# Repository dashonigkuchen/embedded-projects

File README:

# Car seat control (ESP32-C3 / PlatformIO)

Firmware for a DIY car-seat control unit with heating/cooling and battery charging integration.

## Status

- Hardware/feature intent is documented below.
- Current firmware in [src/main.cpp](src/main.cpp) is still the PlatformIO template (no seat-control logic yet).

## What this is (intended)

The overall project is a car seat with:

- Electrical adjustment motors (not handled by this firmware)
- Seat heating and cooling
- A custom battery pack
- A charging module that the ESP32 talks to

This firmware is intended to run on an ESP32-C3 (configured for the Adafruit QT Py ESP32-C3 in [platformio.ini](platformio.ini)).

## Planned functionality

### Heating & cooling control

- A potentiometer provides the user setpoint/input.
- The ESP32 drives heating and cooling via PWM outputs.
- A dedicated “kill/enable” output can disable both heating and cooling.
- Heating also reads a thermistor input; the firmware must enforce temperature safety limits to avoid damage.

### Charging module integration

- Communication with the charging module via I2C.
- An interrupt line from the module to the ESP32 signals events (e.g., charger plugged in).
- An ESP32 output can disable/stop charging (if needed).

### Optional WiFi

- The ESP32 may try to connect to a configured WiFi for monitoring/control.
- WiFi should be power-aware; if it drains too much battery it may be disabled.

## Hardware

This repo contains both firmware and a custom-hardware design.

- Firmware is currently configured for an Adafruit QT Py ESP32-C3 (`adafruit_qtpy_esp32c3` in [platformio.ini](platformio.ini)).
- The KiCad design in [assets/schematics/chris/](assets/schematics/chris/) uses an ESP32-C3 module directly (ESP32-C3-WROOM-02-H4).

### Schematics (screenshots)

These images are exported from the KiCad project and are useful for quickly understanding the blocks:

### Key parts (from the order list)

The order list is in [assets/order/export_cart_20260301_180926.csv](assets/order/export_cart_20260301_180926.csv).

Notable parts from that cart export:

- ESP32 module: ESP32-C3-WROOM-02-H4 (LCSC C2944070), qty 2
- Charger IC: BQ25792RQMR (LCSC C2862876), qty 2 (1–4 cell, up to 5A charger IC)
- Automotive relays: STKF-12V3 (LCSC C771768), qty 10 (12V coil, 15A@14VDC contacts)
- Power MOSFETs: AOD4184A (LCSC C99124), qty 5 (TO-252 / DPAK)
- Small MOSFETs: AO3400A (LCSC C347475), qty 20 (SOT-23)
- Schottky diodes: SS54F (LCSC C5359893), qty 20 (40V / 5A)
- Inductors: CR6045-2R2N (LCSC C7588804), qty 10 (2.2µH)
- NTC thermistor: HNTC-103F3435FA (LCSC C52204610), qty 10 (10k NTC)
- Terminal blocks: MX142R-5.08-08P (LCSC C48688013), qty 1; MX142R-5.08-02P (LCSC C48688007), qty 5

### Signals / nets (as named in the schematic)

If you want the firmware pinout to match the PCB, these are the key named nets to map to ESP32-C3 GPIOs:

- Heater: `HEATER_PWM`, `HEATER_OUT`, `HEATER_POTI`, `HEATER_THERMISTOR`
- Fan/cooling: `FAN_PWM`, `FAN_OUT`, `FAN_POTI`
- Charger (BQ25792): `BQ_SDA`, `BQ_SCL`, `BQ_INT`, `BQ_STAT`, `BQ_CE`, `BQ_ILIM_HIZ`, `BQ_TS`
- Power control: `POWER_EN`, `V_SYSTEM`, `V_SYSTEM_TOGGLE`
- ESP control: `ESP_EN`, `ESP_BOOT`

## Pinout / wiring (from KiCad schematic)

The KiCad schematic places net labels directly on the ESP32-C3 module pins (U1). Based on those labels, the mapping is:

- Heater
	- `HEATER_PWM` -> ESP32-C3 `IO7`
	- `HEATER_POTI` -> ESP32-C3 `TXD`
	- `HEATER_THERMISTOR` -> ESP32-C3 `IO3`

- Fan / cooling
	- `FAN_PWM` -> ESP32-C3 `IO6`
	- `FAN_POTI` -> ESP32-C3 `IO18`

- Charger (BQ25792)
	- `BQ_SDA` -> ESP32-C3 `IO9`
	- `BQ_SCL` -> ESP32-C3 `IO8`
	- `BQ_INT` -> ESP32-C3 `IO19`
	- `BQ_CE` -> ESP32-C3 `IO0`

- USB (debug / flashing)
	- `USB_D+` -> ESP32-C3 `IO2`
	- `USB_D-` -> ESP32-C3 `IO1`

- Boot control
	- `ESP_BOOT` -> ESP32-C3 `IO4`

Notes:

- The schematic also labels `ESP_EN` and `POWER_EN` at pins that are currently named `GND` in the ESP32-C3 symbol. Please verify the custom symbol pinout and/or those net labels before relying on that part of the mapping.

## Build, flash, monitor

Prerequisites:

- PlatformIO (VS Code extension or `pio` CLI)

Commands (from repo root):

- Build: `pio run`
- Upload: `pio run -t upload`
- Serial monitor: `pio device monitor`

If you have multiple serial devices connected, specify the port:

- `pio run -t upload --upload-port /dev/ttyUSB0`
- `pio device monitor --port /dev/ttyUSB0`

## Configuration

TBD:

- WiFi credentials/config mechanism (compile-time constants? `secrets.h`? captive portal?)
- Temperature limits and PWM frequency
- Charging-module parameters (I2C address, thresholds)

## Safety notes

- Seat heaters can overheat if driven blindly; the thermistor should always be enforced with conservative limits.
- Add an independent hardware fuse / cutoff where appropriate; do not rely purely on firmware for safety.

## Roadmap

- Implement PWM outputs for heating/cooling
- Implement potentiometer input + mapping to PWM
- Add thermistor reading + overtemp protection
- Add I2C driver for the charging module + interrupt handling
- Decide whether WiFi is worth the power cost

## License

TBD

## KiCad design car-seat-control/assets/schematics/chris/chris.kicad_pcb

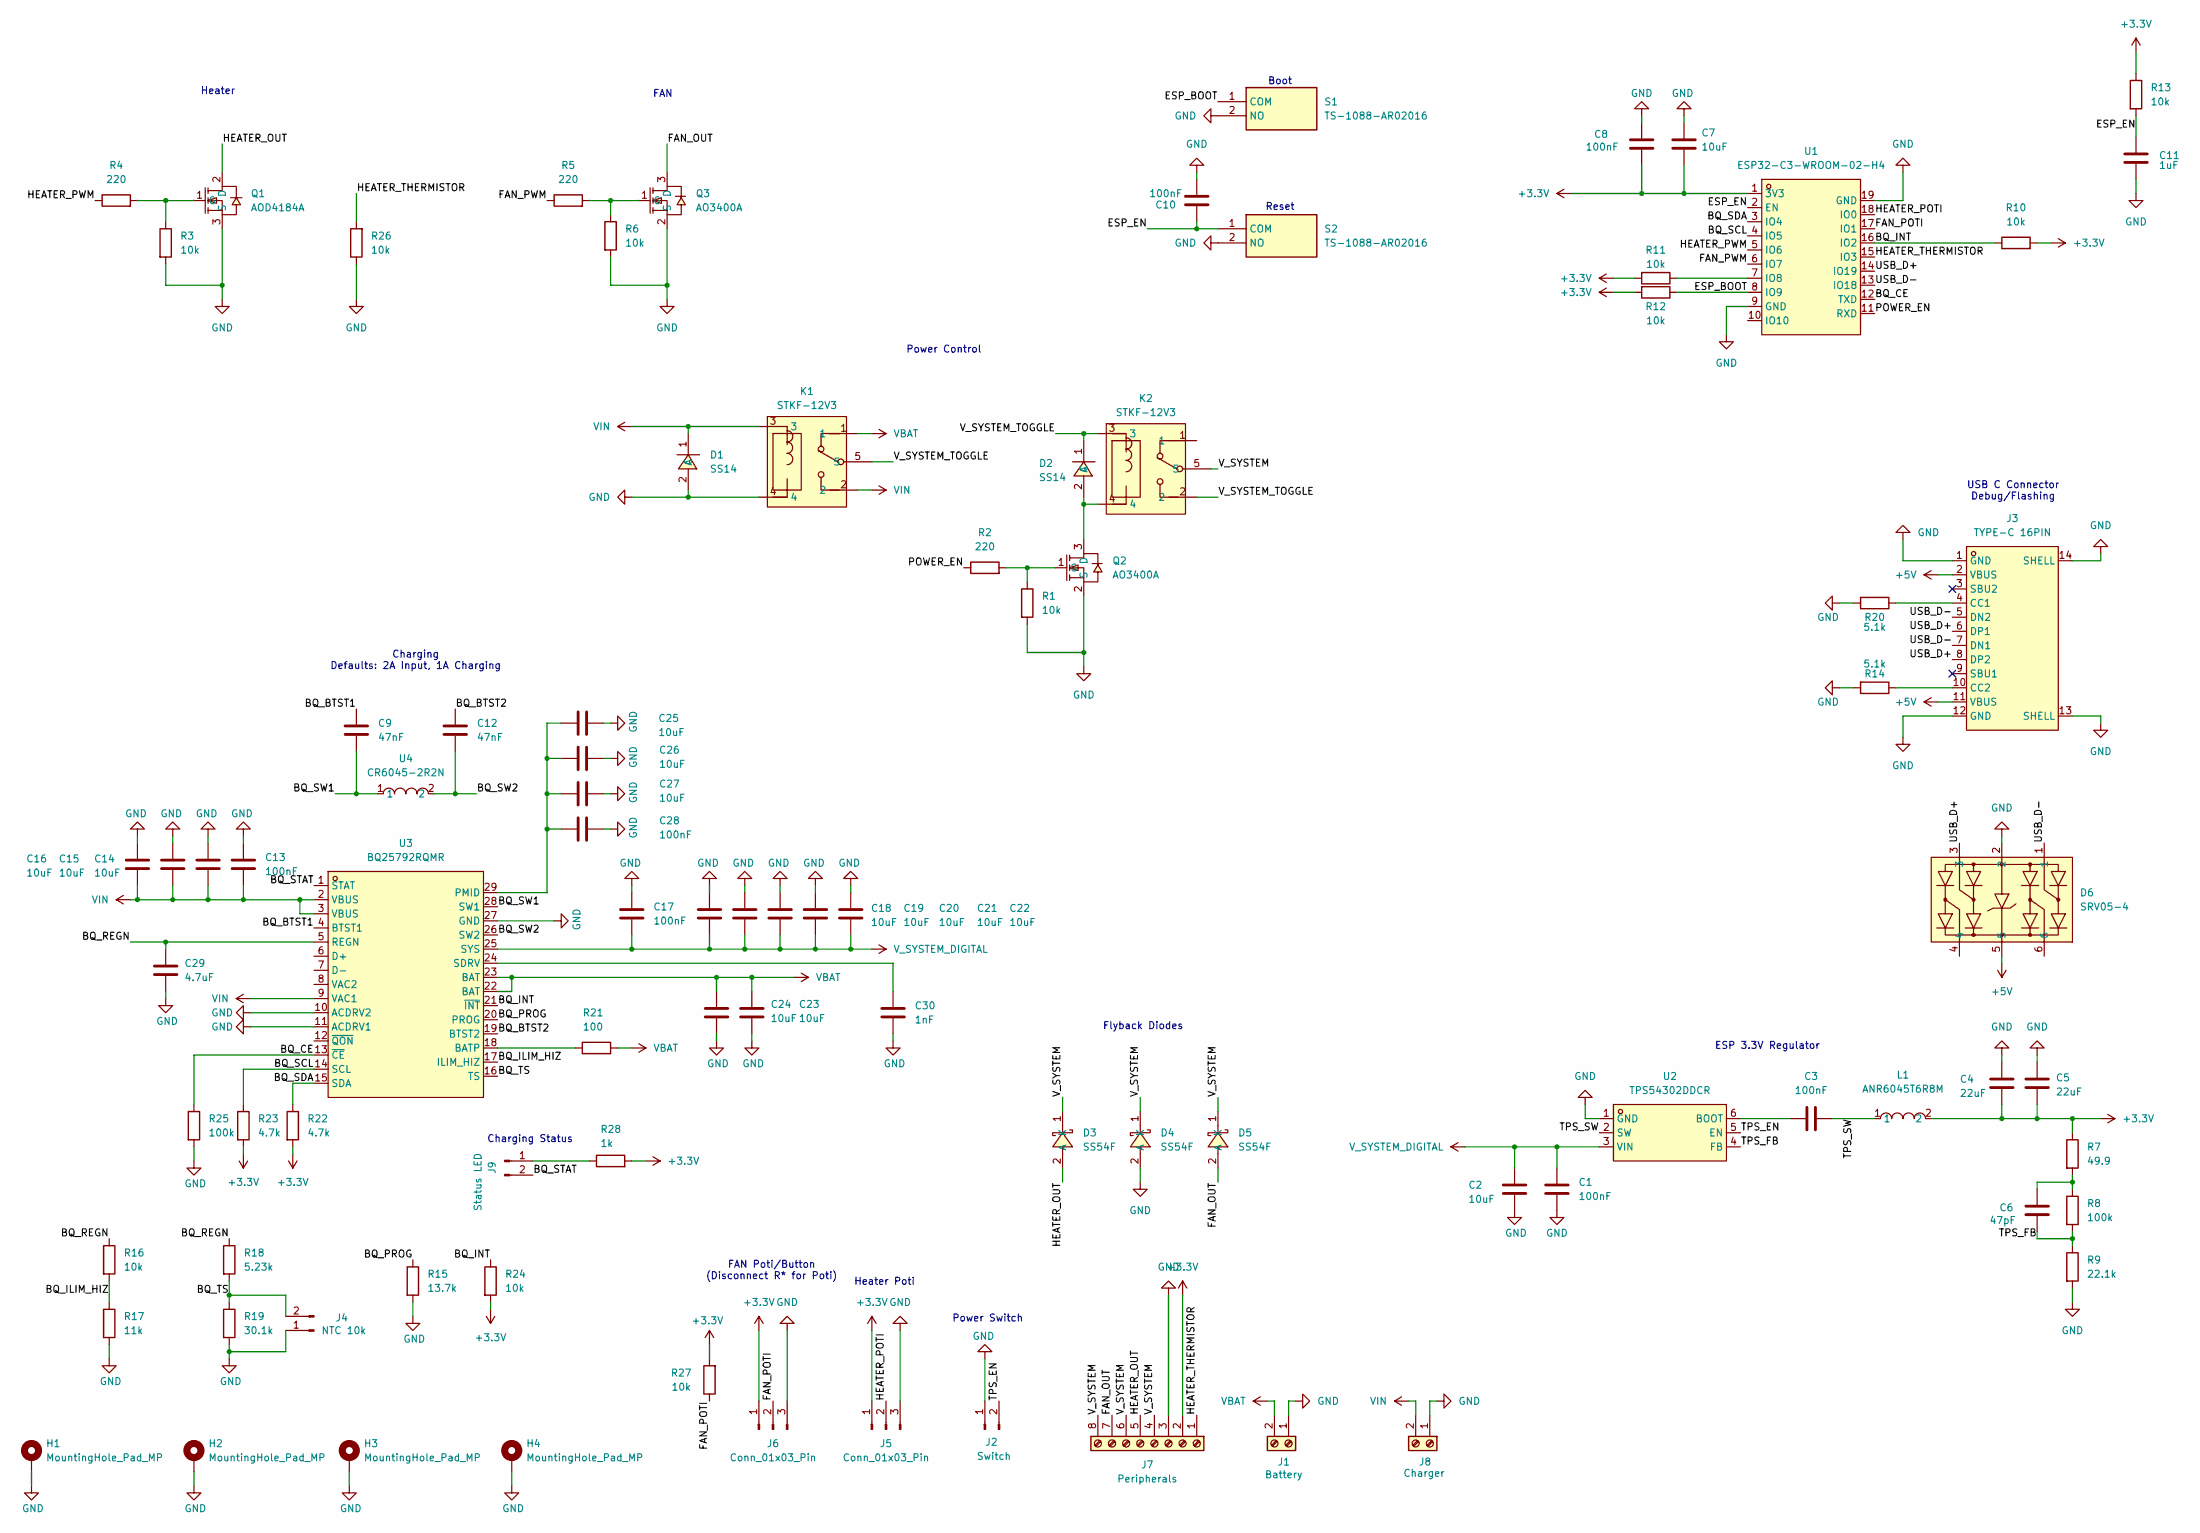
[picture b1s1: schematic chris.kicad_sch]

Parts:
C1, C3, C8, C10, C13, C17, C28: 100nF; C_0603_1608Metric
C2, C7, C14, C15, C16, C18, C19, C20, C21, C22, C23, C24, C25, C26, C27: 10uF; C_0603_1608Metric
C4, C5: 22uF; C_0805_2012Metric
C6: 47pF; C_0603_1608Metric
C9, C12: 47nF; C_0603_1608Metric
C11: 1uF; C_0603_1608Metric
C29: 4.7uF; C_0603_1608Metric
C30: 1nF; C_0603_1608Metric
D1, D2: SS14; SMA_L4.3-W2.6-LS5.0-RD; LCSC Part C2837270
D3, D4, D5: SS54F; SMAF_L3.5-W2.6-LS4.7-RD; LCSC Part C5359893
D6: SRV05-4; SOT-23-6_L2.9-W1.6-P0.95-LS2.8-BL; LCSC Part C558418
H1, H2, H3, H4: MountingHole_Pad_MP; MountingHole_3.2mm_M3_DIN965_Pad
J1: Battery; MX142R-5.08_2
J2: Switch; JST_XH_B2B-XH-A_1x02_P2.50mm_Vertical
J3: TYPE-C 16PIN; USB-C-SMD_TYPE-C-6PIN-2MD-073; LCSC Part C2765186
J4: NTC 10k; JST_XH_B2B-XH-A_1x02_P2.50mm_Vertical
J5, J6: Conn_01x03_Pin; JST_XH_B3B-XH-A_1x03_P2.50mm_Vertical
J7: Peripherals; MX142R-5.08_8
J8: Charger; MX142R-5.08_2
J9: Status LED; PinHeader_1x02_P2.54mm_Vertical
K1, K2: STKF-12V3; RELAY-TH_STKF-12V3; LCSC Part C771768
L1: ANR6045T6R8M; IND-SMD_L6.0-W6.0_ANR6045; LCSC Part C6808110
Q1: AOD4184A; TO-252-2_L6.6-W6.1-P4.57-LS9.9-TL-CW; LCSC Part C99124
Q2, Q3: AO3400A; SOT-23-3_L2.9-W1.3-P1.90-LS2.4-BR; LCSC Part C347475
R1, R3, R6, R10, R11, R12, R13, R16, R24, R26, R27: 10k; R_0603_1608Metric
R2, R4, R5: 220; R_0603_1608Metric
R7: 49.9; R_0603_1608Metric
R8, R25: 100k; R_0603_1608Metric
R9: 22.1k; R_0603_1608Metric
R14, R20: 5.1k; R_0603_1608Metric
R15: 13.7k; R_0603_1608Metric
R17: 11k; R_0603_1608Metric
R18: 5.23k; R_0603_1608Metric
R19: 30.1k; R_0603_1608Metric
R21: 100; R_0603_1608Metric
R22, R23: 4.7k; R_0603_1608Metric
R28: 1k; R_0603_1608Metric
S1, S2: TS-1088-AR02016; SW-SMD_L3.9-W3.0-P4.45; Manufacturer_Part_Number TS-1088-AR02016
U1: ESP32-C3-WROOM-02-H4; WIFIM-SMD_18P-L20.0-W18.0-P1.50; LCSC Part C2944070
U2: TPS54302DDCR; SOT-23-6_L2.9-W1.6-P0.95-LS2.8-BL; LCSC Part C311983
U3: BQ25792RQMR; QFN-29_L4.0-W4.0-P0.40-TL-BQ25792RQMR; LCSC Part C2862876
U4: CR6045-2R2N; IND-SMD_L6.0-W6.0; LCSC Part C7588804

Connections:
+3.3V: C4.2, C5.2, C7.1, C8.1, J5.1, J6.1, J7.2, L1.2, R7.1, R10.2, R11.2, R12.2, R13.1, R22.2, R23.2, R24.2, R27.2, R28.2, U1.1 (3V3)
+5V: D6.5, J3.2 (VBUS), J3.11 (VBUS)
/BQ_BTST1: C9.1, U3.4 (BTST1)
/BQ_BTST2: C12.1, U3.19 (BTST2)
/BQ_CE: R25.1, U1.12 (TXD), U3.13 (~CE)
/BQ_ILIM_HIZ: R16.2, R17.1, U3.17 (ILIM_HIZ)
/BQ_INT: R10.1, R24.1, U1.16 (IO2), U3.21 (~INT)
/BQ_PROG: R15.1, U3.20 (PROG)
/BQ_REGN: C29.2, R16.1, R18.1, U3.5 (REGN)
/BQ_SCL: R23.1, U1.4 (IO5), U3.14 (SCL)
/BQ_SDA: R22.1, U1.3 (IO4), U3.15 (SDA)
/BQ_STAT: J9.2, U3.1 (STAT)
/BQ_SW1: C9.2, U3.28 (SW1), U4.1
/BQ_SW2: C12.2, U3.26 (SW2), U4.2
/BQ_TS: J4.2, R18.2, R19.1, U3.16 (TS)
/ESP_BOOT: R12.1, S1.1 (COM), U1.8 (IO9)
/ESP_EN: C10.1, C11.2, R13.2, S2.1 (COM), U1.2 (EN)
/FAN_OUT: D5.2 (A), J7.7, Q3.3 (D)
/FAN_POTI: J6.2, R27.1, U1.17 (IO1)
/FAN_PWM: R5.1, U1.6 (IO7)
/HEATER_OUT: D3.2 (A), J7.5, Q1.2 (D)
/HEATER_POTI: J5.2, U1.18 (IO0)
/HEATER_PWM: R4.1, U1.5 (IO6)
/HEATER_THERMISTOR: J7.1, R26.2, U1.15 (IO3)
/POWER_EN: R2.1, U1.11 (RXD)
/TPS_EN: J2.2, U2.5 (EN)
/TPS_FB: C6.2, R8.2, R9.1, U2.4 (FB)
/TPS_SW: C3.2, L1.1, U2.2 (SW)
/USB_D+: D6.3, J3.6 (DP1), J3.8 (DP2), U1.14 (IO19)
/USB_D-: D6.1, J3.5 (DN2), J3.7 (DN1), U1.13 (IO18)
/V_SYSTEM: D3.1 (K), D4.1 (K), D5.1 (K), J7.4, J7.6, J7.8, K2.5
/V_SYSTEM_TOGGLE: D2.1 (C), K1.5, K2.2, K2.3
GND: C1.2, C2.2, C4.1, C5.1, C7.2, C8.2, C10.2, C11.1, C13.1, C14.1, C15.1, C16.1, C17.1, C18.1, C19.1, C20.1, C21.1, C22.1, C23.1, C24.1, C25.1, C26.1, C27.1, C28.1, C29.1, C30.2, D1.2 (A), D4.2 (A), D6.2, H1.MP, H2.MP, H3.MP, H4.MP, J1.1, J2.1, J3.1 (GND), J3.12 (GND), J3.13 (SHELL), J3.14 (SHELL), J4.1, J5.3, J6.3, J7.3, J8.1, K1.4, Q1.3 (S), Q2.2 (S), Q3.2 (S), R1.2, R3.2, R6.2, R9.2, R14.2, R15.2, R17.2, R19.2, R20.2, R25.2, R26.1, S1.2 (NO), S2.2 (NO), U1.9 (GND), U1.19 (GND), U2.1 (GND), U3.10 (ACDRV2), U3.11 (ACDRV1), U3.27 (GND)
unnamed: C6.1, R7.2, R8.1
unnamed: D2.2 (A), K2.4, Q2.3 (D)
unnamed: J3.4 (CC1), R20.1
unnamed: J3.10 (CC2), R14.1
unnamed: J9.1, R28.1
unnamed: Q1.1 (G), R3.1, R4.2
unnamed: Q2.1 (G), R1.1, R2.2
unnamed: Q3.1 (G), R5.2, R6.1
unnamed: R11.1, U1.7 (IO8)
unnamed: C3.1, U2.6 (BOOT)
unnamed: R21.1, U3.18 (BATP)
unnamed: C25.2, C26.2, C27.2, C28.2, U3.29 (PMID)
unnamed: C30.1, U3.24 (SDRV)
VBAT: C23.2, C24.2, J1.2, K1.1, R21.2, U3.22 (BAT), U3.23 (BAT)
VIN: C13.2, C14.2, C15.2, C16.2, D1.1 (C), J8.2, K1.2, K1.3, U3.2 (VBUS), U3.3 (VBUS), U3.9 (VAC1)
V_SYSTEM_DIGITAL: C1.1, C2.1, C17.2, C18.2, C19.2, C20.2, C21.2, C22.2, U2.3 (VIN), U3.25 (SYS)

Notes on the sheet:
Power Control
Reset
FAN
Heater
Charging Defaults: 2A Input, 1A Charging
Boot
Flyback Diodes
Power Switch
FAN Poti/Button (Disconnect R* for Poti)
Charging Status
Heater Poti
ESP 3.3V Regulator
USB C Connector Debug/Flashing

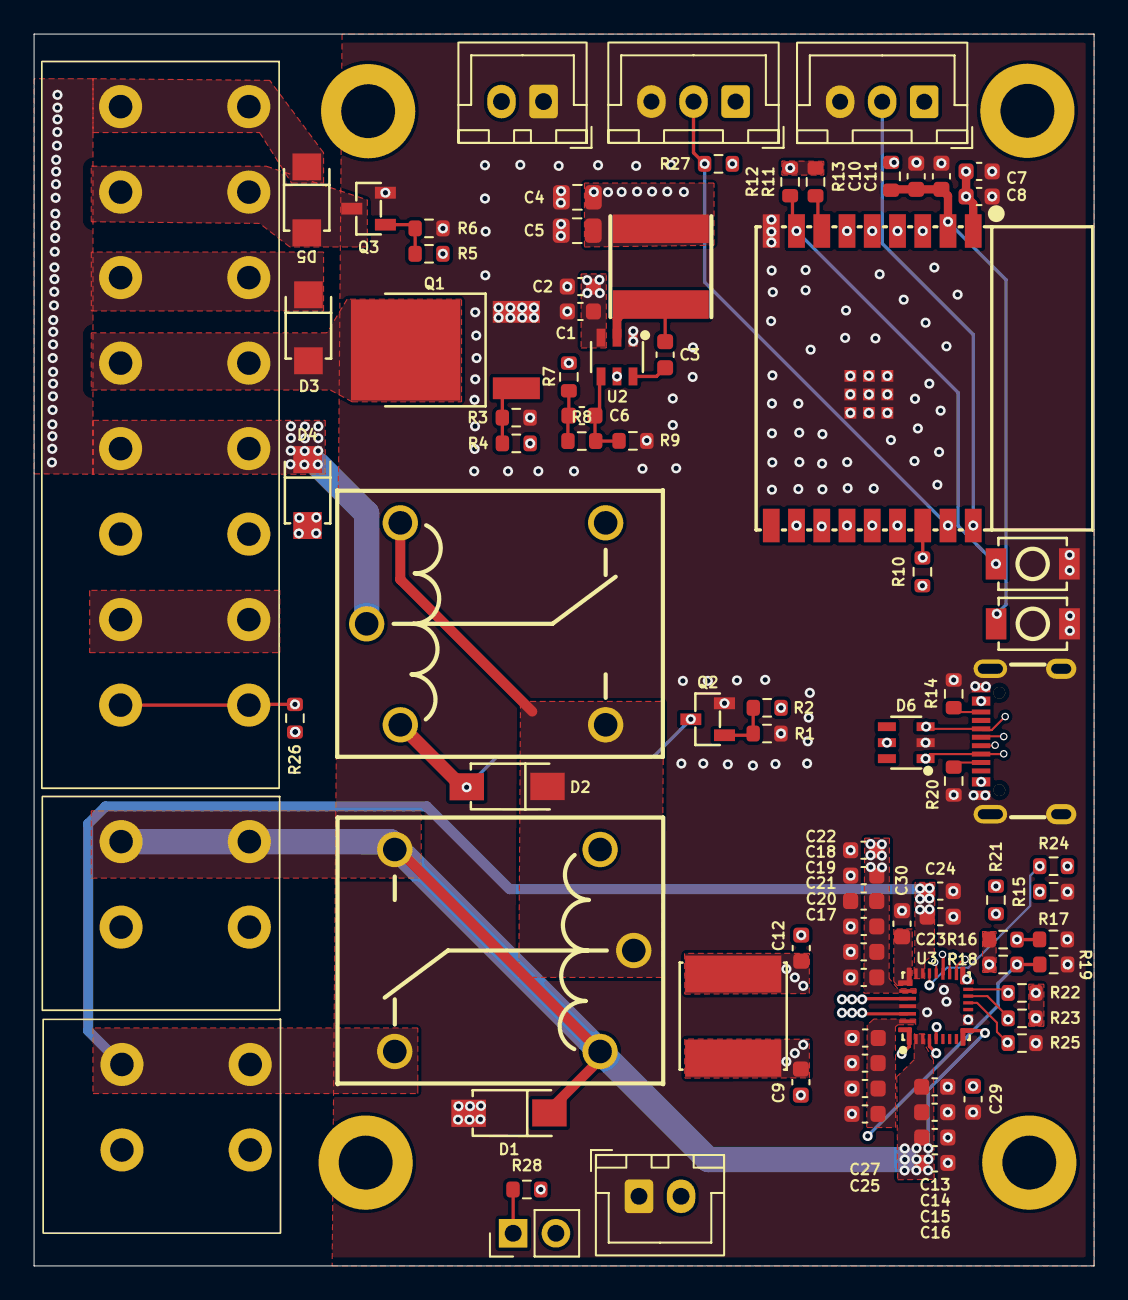
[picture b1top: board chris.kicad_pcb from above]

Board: 6 copper layers, 63.0 x 73.2 mm, 89 parts (0 on the bottom side), 49 nets.

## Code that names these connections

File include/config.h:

#pragma once

// ==========================================================================
//  Car Seat Control – Configuration
//
//  Every tuneable parameter lives here so the rest of the code stays clean.
//  Change pins, limits or timing here – no need to touch logic files.
// ==========================================================================

#include <cstdint>

// ─── Pin assignments (from KiCad schematic) ─────────────────────────
//
// WARNING  On the ESP32-C3 only GPIO 0-5 support analogRead (ADC).
//          HEATER_POTI (GPIO21/TXD) and FAN_POTI (GPIO18) are NOT ADC-capable.
//          If you use analog potentiometers, you must re-route those signals
//          to ADC-capable pins or add an external ADC.  The firmware will
//          still compile, but analogRead() on those pins returns 0.

// Heater
static constexpr uint8_t PIN_HEATER_PWM   =  7;   // PWM to heater MOSFET gate
static constexpr uint8_t PIN_HEATER_POTI  = 21;   // Potentiometer input  (TXD)
static constexpr uint8_t PIN_HEATER_THERM =  3;   // NTC thermistor       (ADC1_CH3)

// Fan / Cooling
static constexpr uint8_t PIN_FAN_PWM      =  6;   // PWM to fan MOSFET gate
static constexpr uint8_t PIN_FAN_POTI     = 18;   // Potentiometer input

// Charger (BQ25792)
static constexpr uint8_t PIN_BQ_SDA       =  9;   // I2C data
static constexpr uint8_t PIN_BQ_SCL       =  8;   // I2C clock
static constexpr uint8_t PIN_BQ_INT       = 19;   // Interrupt (active-low)
static constexpr uint8_t PIN_BQ_CE        =  0;   // Charge-Enable (active-low)

// ─── ADC ─────────────────────────────────────────────────────────────
static constexpr uint8_t  ADC_BITS      = 12;
static constexpr uint16_t ADC_MAX_VALUE = (1 << ADC_BITS) - 1;          // 4095

// ─── PWM ─────────────────────────────────────────────────────────────
static constexpr uint32_t HEATER_PWM_FREQ     =  1000;  // Hz  – low for resistive load
static constexpr uint8_t  HEATER_PWM_RES      =     8;  // bits
static constexpr uint16_t HEATER_PWM_MAX_DUTY = (1 << HEATER_PWM_RES) - 1;  // 255 for 8-bit

static constexpr uint32_t FAN_PWM_FREQ        = 25000;  // Hz  – 25 kHz for quiet fan
static constexpr uint8_t  FAN_PWM_RES         =     8;  // bits
static constexpr uint16_t FAN_PWM_MAX_DUTY    = (1 << FAN_PWM_RES) - 1;     // 255 for 8-bit

// ─── NTC thermistor ──────────────────────────────────────────────────
//  10 kΩ NTC, B = 3435, voltage-divider with 10 kΩ pull-up to 3.3 V:
//    3.3 V ──[R_PULLUP]── ADC ──[NTC]── GND
static constexpr float NTC_R25       = 10000.0f;   // Ω at 25 °C
static constexpr float NTC_BETA      =  3435.0f;   // B-parameter
static constexpr float NTC_R_PULLUP  = 10000.0f;   // pull-up Ω
static constexpr float NTC_T25_K     =   298.15f;  // 25 °C in Kelvin

// ─── Temperature safety ─────────────────────────────────────────────
static constexpr float HEATER_TEMP_LIMIT      = 45.0f;   // °C  – heater OFF above this
static constexpr float HEATER_TEMP_HYSTERESIS =  5.0f;   // °C  – re-enable below (limit − hyst)
static constexpr float TEMP_SENSOR_MIN        = -10.0f;  // °C  – below → sensor fault
static constexpr float TEMP_SENSOR_MAX        =  80.0f;  // °C  – above → sensor fault

// ─── BQ25792 charger ────────────────────────────────────────────────
static constexpr uint8_t  BQ25792_I2C_ADDR      = 0x6B;
static constexpr uint16_t BQ_CHARGE_VOLTAGE_MV   = 12600;  // 3S × 4.2 V
static constexpr uint16_t BQ_CHARGE_CURRENT_MA   =  2000;  // mA
static constexpr uint16_t BQ_MIN_SYS_VOLTAGE_MV  =  9000;  // 3S × 3.0 V
static constexpr uint16_t BQ_INPUT_CURRENT_MA    =  3000;  // mA  (adapter limit)
static constexpr uint8_t  BQ_INPUT_VOLTAGE_100MV =    42;  // × 100 mV → 4.2 V min VINDPM

// ─── Timing ─────────────────────────────────────────────────────────
static constexpr unsigned long LOOP_INTERVAL_MS       =   50;  // 20 Hz control loop
static constexpr unsigned long THERM_READ_INTERVAL_MS =  500;  // thermistor sample rate
static constexpr unsigned long CHARGER_POLL_MS        = 1000;  // charger status poll
static constexpr unsigned long STATUS_PRINT_MS        = 2000;  // serial debug log
static constexpr uint32_t     WDT_TIMEOUT_S          =    5;  // watchdog (seconds)

// ─── Serial ─────────────────────────────────────────────────────────
static constexpr unsigned long SERIAL_BAUD = 115200;

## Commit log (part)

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2026-03-03 Initial version with a simple README
2026-03-04 Move assets, enhance readme
2026-03-04 Add charger, heater, and fan control implementations with configuration
2026-03-06 Fix some issues found by copilot
2026-03-06 Move into subfolder
2026-03-06 Add initial project structure and configuration files for ESP32 Relay Module
2026-03-09 Update assets with newest version of schematics/pcb
2026-03-16 update esp32 relay module project to use esphome
2026-04-01 new assets for car-seat-control
2026-04-08 Initial plan
2026-04-08 Add detailed car-seat-control TODO roadmap
    Agent-Logs-Url: https://github.com/dashonigkuchen/embedded-projects/sessions/6158e524-a289-477d-863c-a856973e276d
